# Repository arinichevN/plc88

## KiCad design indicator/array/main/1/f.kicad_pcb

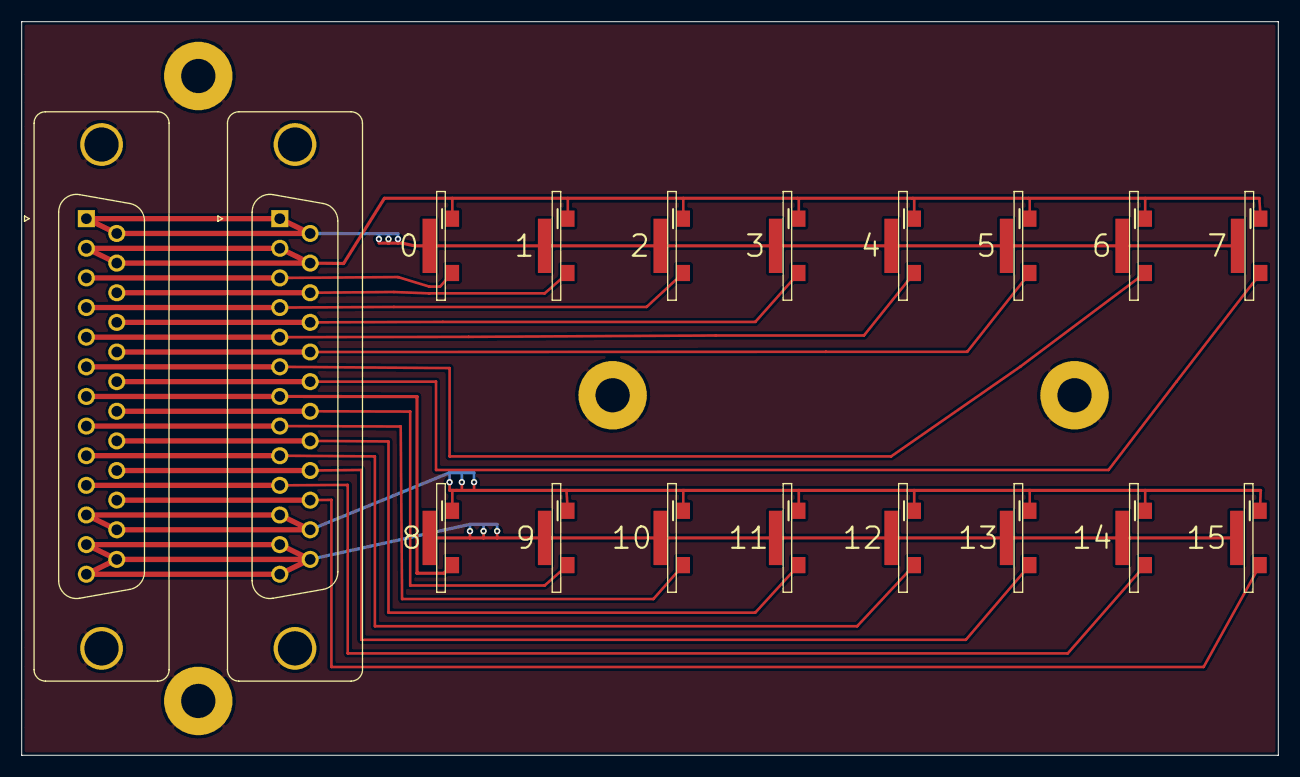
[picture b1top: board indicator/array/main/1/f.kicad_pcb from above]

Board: 2 copper layers, 117.5 x 68.6 mm, 22 parts (0 on the bottom side), 21 nets.

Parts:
H1, H2, H3, H4: MountingHole_Pad; MountingHole_3.2mm_M3_Pad
J1, J2: DB25_Female_MountingHoles; DSUB-25_Female_Vertical_P2.77x2.84mm_MountingHoles
J3, J4, J5, J6, J7, J8, J9, J10, J11, J12, J13, J14, J15, J16, J17, J18: indicator_channel_in_i

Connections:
GND: H1.1, H2.1, H3.1, H4.1, J1.0, J2.0
L0: J1.3, J2.3, J3.2
L1: J1.16, J2.16, J4.2
L2: J1.4, J2.4, J5.2
L3: J1.17, J2.17, J6.2
L4: J1.5, J2.5, J7.2
L5: J1.18, J2.18, J8.2
L6: J1.6, J2.6, J9.2
L7: J1.19, J2.19, J10.2
L8: J1.7, J2.7, J11.2
L9: J1.20, J2.20, J12.2
L10: J1.8, J2.8, J13.2
L11: J1.21, J2.21, J14.2
L12: J1.9, J2.9, J15.2
L13: J1.22, J2.22, J16.2
L14: J1.10, J2.10, J17.2
L15: J1.23, J2.23, J18.2
VM0_7: J1.1, J1.14, J2.1, J2.14, J3.3, J4.3, J5.3, J6.3, J7.3, J8.3, J9.3, J10.3
VM8_15: J1.12, J1.13, J1.25, J2.12, J2.13, J2.25, J11.3, J12.3, J13.3, J14.3, J15.3, J16.3, J17.3, J18.3
VP0_7: J1.2, J1.15, J2.2, J2.15, J3.1, J4.1, J5.1, J6.1, J7.1, J8.1, J9.1, J10.1
VP8_15: J1.11, J1.24, J2.11, J2.24, J11.1, J12.1, J13.1, J14.1, J15.1, J16.1, J17.1, J18.1

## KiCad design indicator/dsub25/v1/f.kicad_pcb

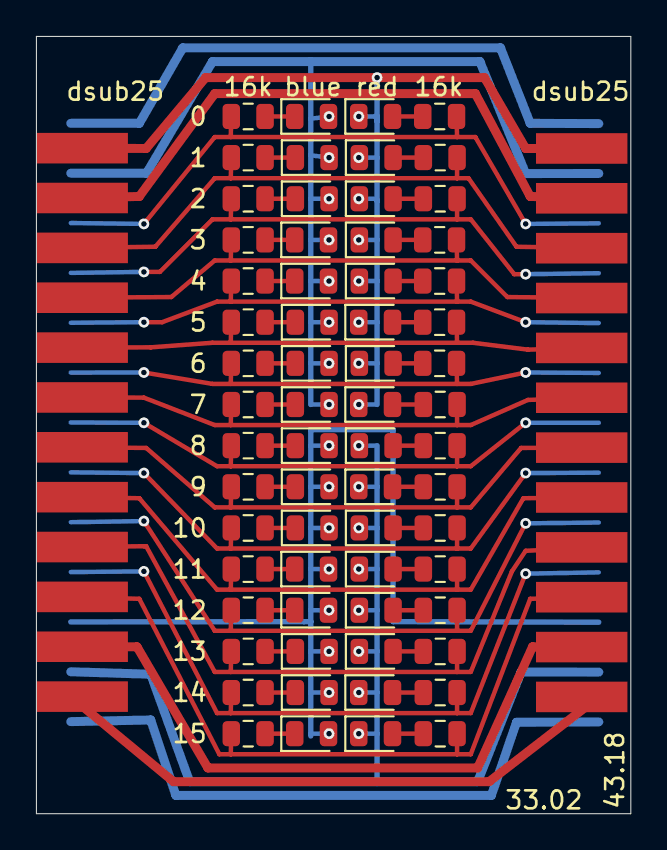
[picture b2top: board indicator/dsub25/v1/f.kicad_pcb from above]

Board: 2 copper layers, 33.0 x 43.2 mm, 66 parts (0 on the bottom side), 52 nets.

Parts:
D1, D2, D3, D4, D5, D6, D7, D8, D9, D10, D11, D12, D13, D14, D15, D16, D17, D18, D19, D20, D21, D22, D23, D24, D25, D26, D27, D28, D29, D30, D31, D32: LED; LED_0805_2012Metric
J1, J2: DB25; dsub25_edge
R1, R2, R3, R4, R5, R6, R7, R8, R9, R10, R11, R12, R13, R14, R15, R16, R17, R18, R19, R20, R21, R22, R23, R24, R25, R26, R27, R28, R29, R30, R31, R32: 16k; R_0805_2012Metric

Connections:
GND0_7: D1.1, D3.1, D5.1, D7.1, D9.1, D11.1, D13.1, D15.1, J1.1, J1.14, J2.1, J2.14
GND8_15: D17.1, D19.1, D21.1, D23.1, D25.1, D27.1, D29.1, D31.1, J1.12, J1.13, J1.25, J2.12, J2.13, J2.25
L0: J1.3, J2.3, R1.2, R2.2
L1: J1.16, J2.16, R3.2, R4.2
L2: J1.4, J2.4, R5.2, R6.2
L3: J1.17, J2.17, R7.2, R8.2
L4: J1.5, J2.5, R9.2, R10.2
L5: J1.18, J2.18, R11.2, R12.2
L6: J1.6, J2.6, R13.2, R14.2
L7: J1.19, J2.19, R15.2, R16.2
L8: J1.7, J2.7, R17.2, R18.2
L9: J1.20, J2.20, R19.2, R20.2
L10: J1.8, J2.8, R21.2, R22.2
L11: J1.21, J2.21, R23.2, R24.2
L12: J1.9, J2.9, R25.2, R26.2
L13: J1.22, J2.22, R27.2, R28.2
L14: J1.10, J2.10, R29.2, R30.2
L15: J1.23, J2.23, R31.2, R32.2
unnamed: D1.2, R1.1
unnamed: D2.1, R2.1
unnamed: D3.2, R3.1
unnamed: D4.1, R4.1
unnamed: D5.2, R5.1
unnamed: D6.1, R6.1
unnamed: D7.2, R7.1
unnamed: D8.1, R8.1
unnamed: D9.2, R9.1
unnamed: D10.1, R10.1
unnamed: D11.2, R11.1
unnamed: D12.1, R12.1
unnamed: D13.2, R13.1
unnamed: D14.1, R14.1
unnamed: D15.2, R15.1
unnamed: D16.1, R16.1
unnamed: D17.2, R17.1
unnamed: D18.1, R18.1
unnamed: D19.2, R19.1
unnamed: D20.1, R20.1
unnamed: D21.2, R21.1
unnamed: D22.1, R22.1
unnamed: D23.2, R23.1
unnamed: D24.1, R24.1
unnamed: D25.2, R25.1
unnamed: D26.1, R26.1
unnamed: D27.2, R27.1
unnamed: D28.1, R28.1
unnamed: D29.2, R29.1
unnamed: D30.1, R30.1
unnamed: D31.2, R31.1
unnamed: D32.1, R32.1
V0_7: D2.2, D4.2, D6.2, D8.2, D10.2, D12.2, D14.2, D16.2, J1.2, J1.15, J2.2, J2.15
V8_15: D18.2, D20.2, D22.2, D24.2, D26.2, D28.2, D30.2, D32.2, J1.11, J1.24, J2.11, J2.24

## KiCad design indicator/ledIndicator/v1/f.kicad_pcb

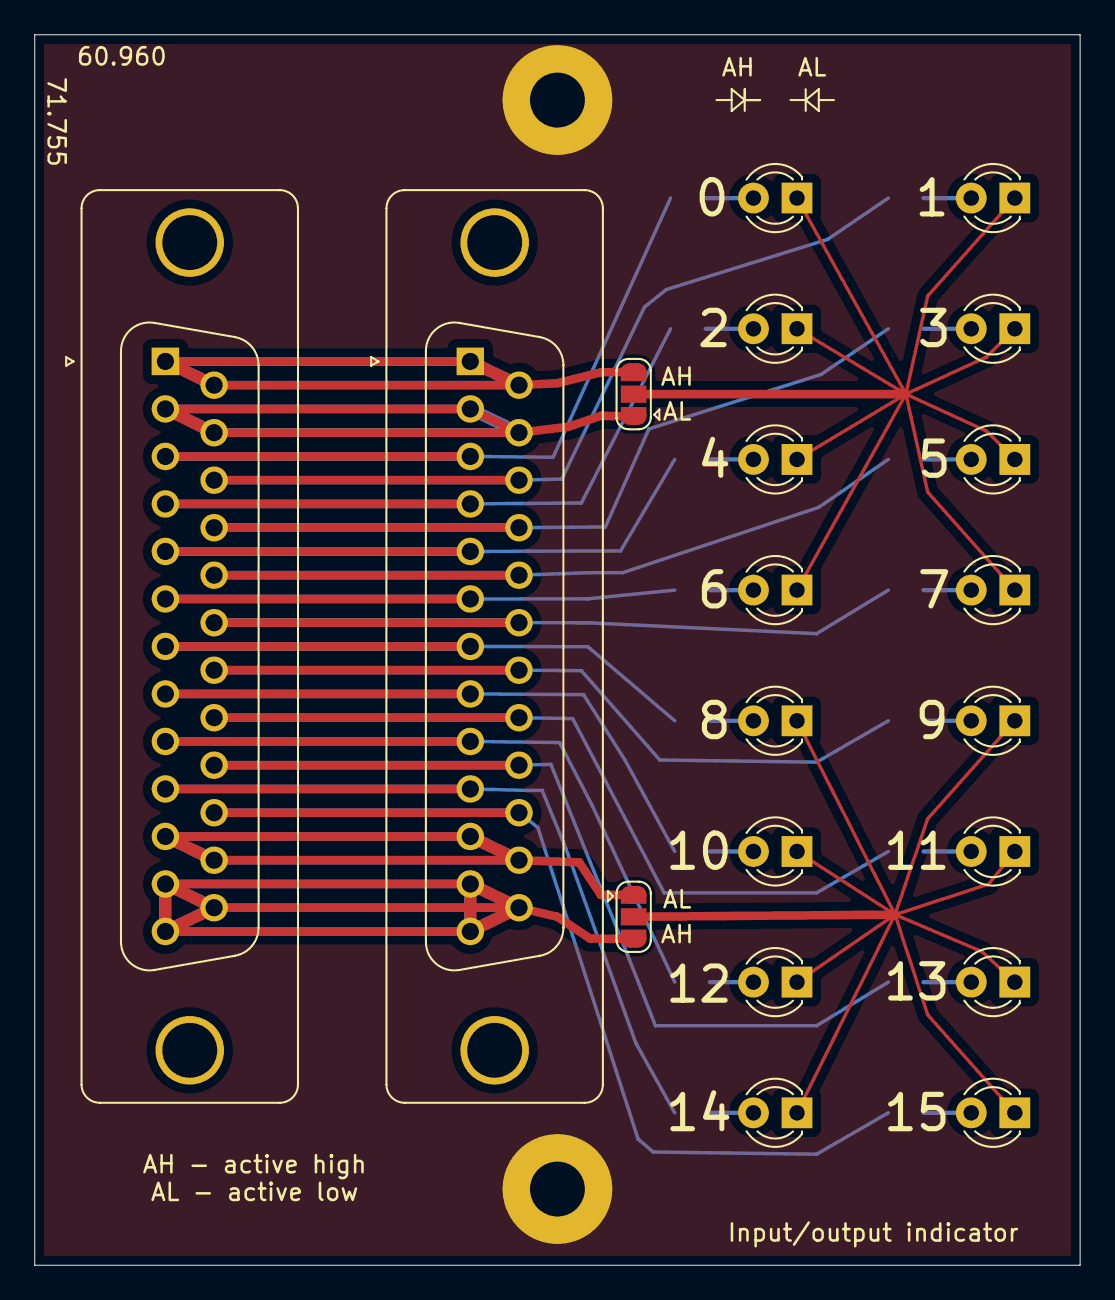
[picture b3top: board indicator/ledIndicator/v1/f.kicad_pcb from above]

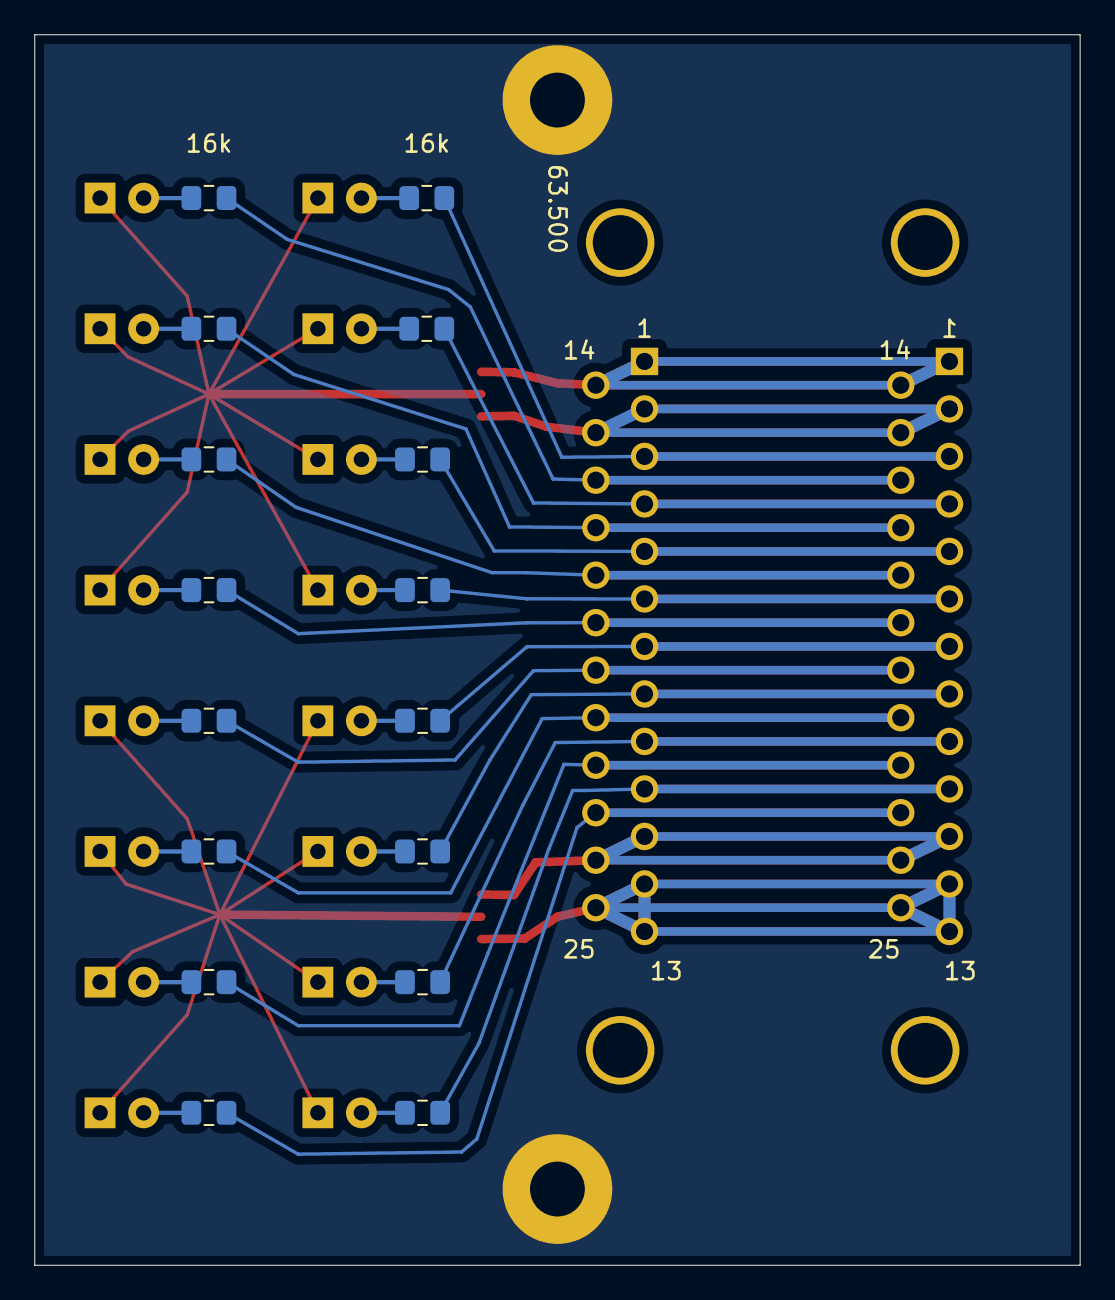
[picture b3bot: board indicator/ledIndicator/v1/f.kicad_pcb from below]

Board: 2 copper layers, 61.0 x 71.8 mm, 38 parts (16 on the bottom side), 39 nets.

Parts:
D1: 0; LED_D3.0mm
D2: 1; LED_D3.0mm
D3: 2; LED_D3.0mm
D4: 3; LED_D3.0mm
D5: 4; LED_D3.0mm
D6: 5; LED_D3.0mm
D7: 6; LED_D3.0mm
D8: 7; LED_D3.0mm
D9: 8; LED_D3.0mm
D10: 9; LED_D3.0mm
D11: 10; LED_D3.0mm
D12: 11; LED_D3.0mm
D13: 12; LED_D3.0mm
D14: 13; LED_D3.0mm
D15: 14; LED_D3.0mm
D16: 15; LED_D3.0mm
H1, H2: MountingHole_Pad; MountingHole_3.2mm_M3_Pad
J1, J2: DB25_Female; DSUB-25_Female_Vertical_P2.77x2.84mm_MountingHoles
JP1, JP2: Jumper_3_Open; SolderJumper-3_P1.3mm_Open_RoundedPad1.0x1.5mm
R1, R2, R3, R4, R5, R6, R7, R8, R9, R10, R11, R12, R13, R14, R15, R16: 16k; R_0805_2012Metric_Pad1.15x1.40mm_HandSolder

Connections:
GND: H1.1, H2.1
L0: J1.3, J2.3, R1.2
L1: J1.16, J2.16, R2.2
L2: J1.4, J2.4, R3.2
L3: J1.17, J2.17, R4.2
L4: J1.5, J2.5, R5.2
L5: J1.18, J2.18, R6.2
L6: J1.6, J2.6, R7.2
L7: J1.19, J2.19, R8.2
L8: J1.7, J2.7, R9.2
L9: J1.20, J2.20, R10.2
L10: J1.8, J2.8, R11.2
L11: J1.21, J2.21, R12.2
L12: J1.9, J2.9, R13.2
L13: J1.22, J2.22, R14.2
L14: J1.10, J2.10, R15.2
L15: J1.23, J2.23, R16.2
unnamed: D1.1, D2.1, D3.1, D4.1, D5.1, D6.1, D7.1, D8.1, JP1.2
unnamed: D1.2, R1.1
unnamed: D2.2, R2.1
unnamed: D3.2, R3.1
unnamed: D4.2, R4.1
unnamed: D5.2, R5.1
unnamed: D6.2, R6.1
unnamed: D7.2, R7.1
unnamed: D8.2, R8.1
unnamed: D9.2, R9.1
unnamed: D9.1, D10.1, D11.1, D12.1, D13.1, D14.1, D15.1, D16.1, JP2.2
unnamed: D10.2, R10.1
unnamed: D11.2, R11.1
unnamed: D12.2, R12.1
unnamed: D13.2, R13.1
unnamed: D14.2, R14.1
unnamed: D15.2, R15.1
unnamed: D16.2, R16.1
VM0_7: J1.1, J1.14, J2.1, J2.14, JP1.3
VM8_15: J1.12, J1.13, J1.25, J2.12, J2.13, J2.25, JP2.3
VP0_7: J1.2, J1.15, J2.2, J2.15, JP1.1
VP8_15: J1.11, J1.24, J2.11, J2.24, JP2.1

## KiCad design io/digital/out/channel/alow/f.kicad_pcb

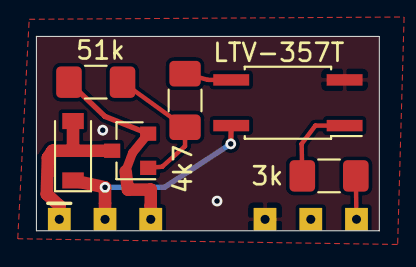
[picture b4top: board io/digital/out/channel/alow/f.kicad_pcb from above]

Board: 2 copper layers, 19.1 x 10.8 mm, 7 parts (0 on the bottom side), 8 nets.

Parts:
D1: 1N4148W; D_SOD-123
J1: dio_channel_i; dio_channel_im
Q1: BC817; SOT-23
R1: 51k; R_1206_3216Metric_Pad1.42x1.75mm_HandSolder
R2: 4k7; R_1206_3216Metric_Pad1.42x1.75mm_HandSolder
R3: 3k; R_1206_3216Metric_Pad1.42x1.75mm_HandSolder
U1: LTV-357T; SO-4_4.4x3.6mm_P2.54mm

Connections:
GND: J1.4, U1.2
IN: J1.6, R3.2
unnamed: Q1.1, R1.2, R2.1
unnamed: R2.2, U1.3
unnamed: R3.1, U1.1
OUT: D1.2, J1.1, Q1.3
VINM: J1.3, Q1.2, R1.1
VINP: D1.1, J1.2, U1.4

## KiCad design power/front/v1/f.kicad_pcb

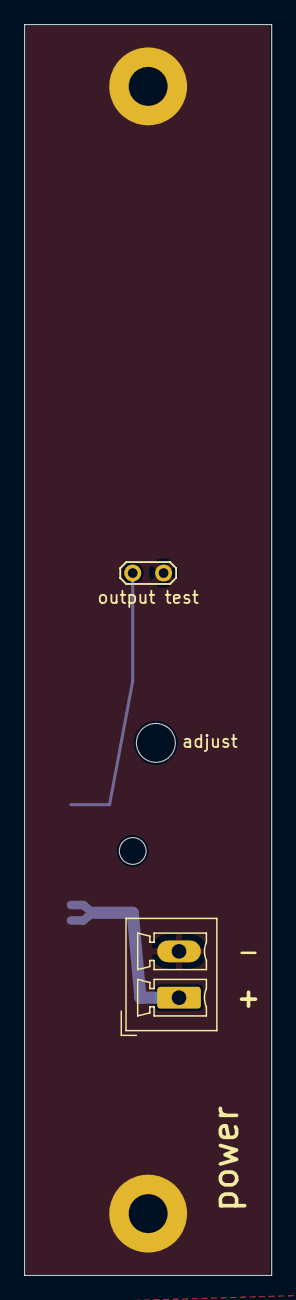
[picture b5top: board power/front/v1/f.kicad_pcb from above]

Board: 2 copper layers, 20.3 x 102.9 mm, 7 parts (0 on the bottom side), 3 nets.

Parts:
H1, H2: MountingHole_Pad; MountingHole_3.2mm_M3_Pad
H3: adjust; MountingHole_3.2mm_M3_DIN965
H4: power led; MountingHole_2.2mm_M2_DIN965
J1: fm_power_i
J10: input; PhoenixContact_MCV_1,5_2-G-3.81_1x02_P3.81mm_Vertical
TP1: output test; TestPoint_2Pads_Pitch2.54mm_Drill0.8mm

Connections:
GND: H1.1, H2.1, J1.2, J1.4, J1.5, J10.2, TP1.2
VIN: J1.1, J10.1
VOUT: J1.3, TP1.1
